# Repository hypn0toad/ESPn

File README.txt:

This project consists of a multi platform communication device that was intended to be used as a gift / could be considered an art project. 

arduino_main/    = the main arduino code for the devices
arduino_slave/   = test code to be used in a prototype system. allows a serial interface on the PC (uart) to communicate through the arduino back and forth from an imp
imp/            = the imp code, needs to be loaded in the planner to both imps
docs/           = partslist/BOM, pinout reference, issue tracking (future ideas & bugs)
docs/datasheets = random datasheets for parts used in the design
docs/schematics = schematic and PWB for main board; schematic for logic level slave board

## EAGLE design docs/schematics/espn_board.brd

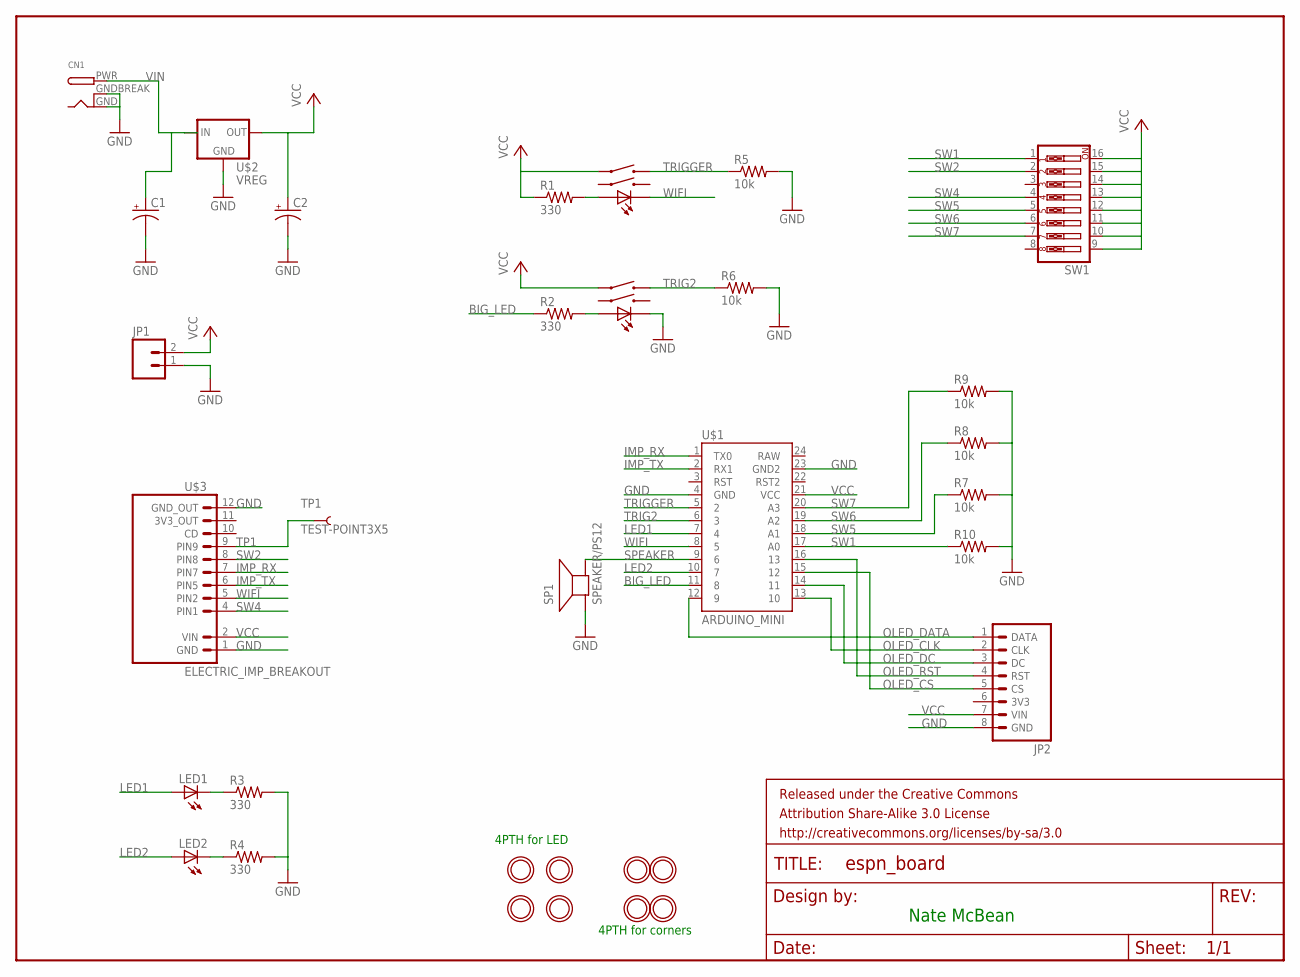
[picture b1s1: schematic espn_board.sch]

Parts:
ACK: LED_TACTILE_BUTTON
C1, C2: CAP_POLPTH2; CPOL-RADIAL-10UF-25V
CN1: DCBARRELPTH; DCJACK_2MM_PTH
FRAME1: FRAME-LETTER; CREATIVE_COMMONS
JP1: M02PTH; 1X02
JP2: OLED128X641X08; OLED_128X64
LED1, LED2: LED5MM
R1, R2, R3, R4: 330; R0805
R5, R6, R7, R8, R9, R10: 10k; R0805
SEND: LED_TACTILE_BUTTON
SP1: SPEAKER/PS12; PS12
SW1: SW_DIP-8; DIPSWITCH-08
TP1: TEST-POINT3X5; PAD.03X.05
U$1: ARDUINO_MINI
U$2: VREG; 78XXL
U$3: ELECTRIC_IMP_BREAKOUT
U$5, U$6, U$7, U$8, U$9, U$10, U$11, U$12: MOUNTINGHOLE2.5; MOUNTINGHOLE_2.5_PLATED

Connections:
BIG_LED: R2.1, U$1.11 (8)
GND: ACK.LEDC, C1.2 (-), C2.2 (-), CN1.GND, CN1.GNDBREAK, JP1.1, JP2.8 (GND), R3.2, R4.2, R5.2, R6.2, R7.2, R8.2, R9.2, R10.2, SP1.P$1 (+), U$1.4 (GND), U$1.23 (GND2), U$2.IN (GND), U$3.1 (GND), U$3.12 (GND_OUT)
IMP_RX: U$1.1 (TX0), U$3.7 (PIN7)
IMP_TX: U$1.2 (RX1), U$3.6 (PIN5)
LED1: LED1.A, U$1.7 (4)
LED2: LED2.A, U$1.10 (7)
unnamed: R1.2, SEND.LEDA
unnamed: ACK.LEDA, R2.2
unnamed: LED1.K (C), R3.1
unnamed: LED2.K (C), R4.1
OLED_CLK: JP2.2 (CLK), U$1.13 (10)
OLED_CS: JP2.5 (CS), U$1.15 (12)
OLED_DATA: JP2.1 (DATA), U$1.12 (9)
OLED_DC: JP2.3 (DC), U$1.14 (11)
OLED_RST: JP2.4 (RST), U$1.16 (13)
SPEAKER: SP1.P$2 (-), U$1.9 (6)
SW1: R10.1, SW1.1, U$1.17 (A0)
SW2: SW1.2, U$3.8 (PIN8)
SW4: SW1.4, U$3.4 (PIN1)
SW5: R7.1, SW1.5, U$1.18 (A1)
SW6: R8.1, SW1.6, U$1.19 (A2)
SW7: R9.1, SW1.7, U$1.20 (A3)
TP1: TP1.P$1, U$3.9 (PIN9)
TRIG2: ACK.SWA2, R6.1, U$1.6 (3)
TRIGGER: R5.1, SEND.SWA2, U$1.5 (2)
VCC: ACK.SWA1, C2.1 (+), JP1.2, JP2.7 (VIN), R1.1, SEND.SWA1, SW1.9, SW1.10, SW1.11, SW1.12, SW1.13, SW1.14, SW1.15, SW1.16, U$1.21 (VCC), U$2.GND (OUT), U$3.2 (VIN)
VIN: C1.1 (+), CN1.PWR, U$2.OUT (IN)
WIFI: SEND.LEDC, U$1.8 (5), U$3.5 (PIN2)

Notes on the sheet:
Nate McBean
4PTH for LED
4PTH for corners

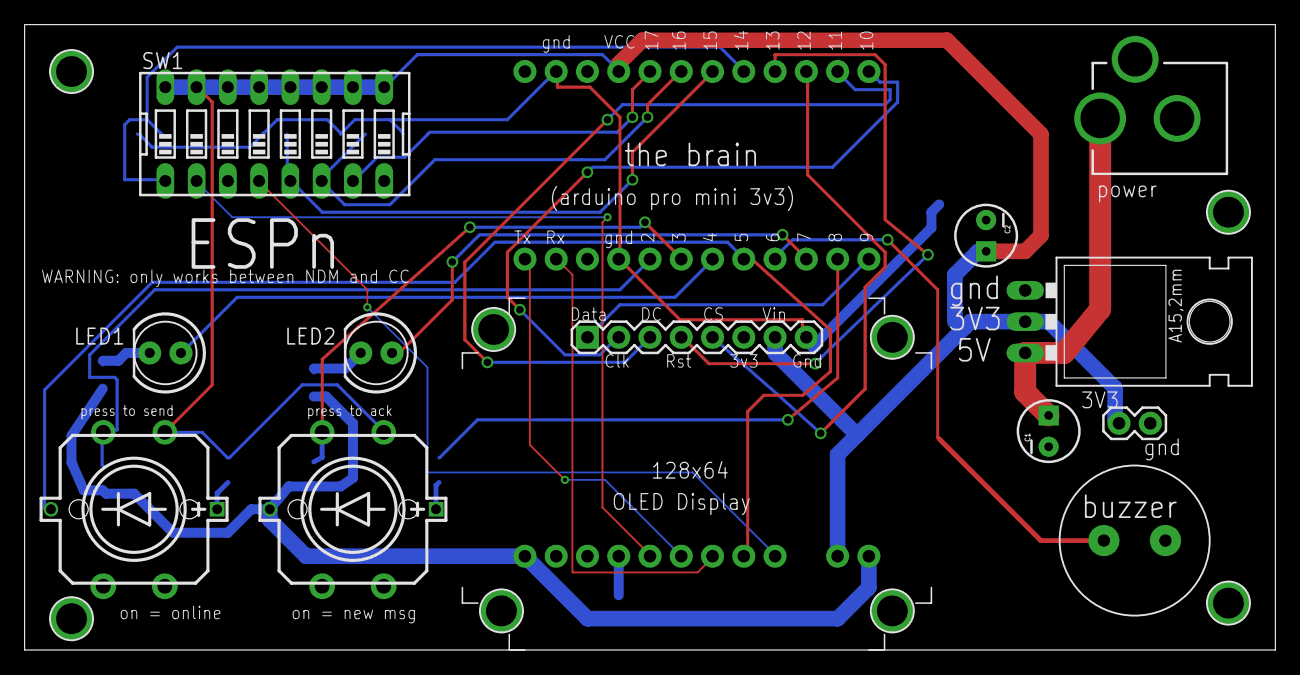
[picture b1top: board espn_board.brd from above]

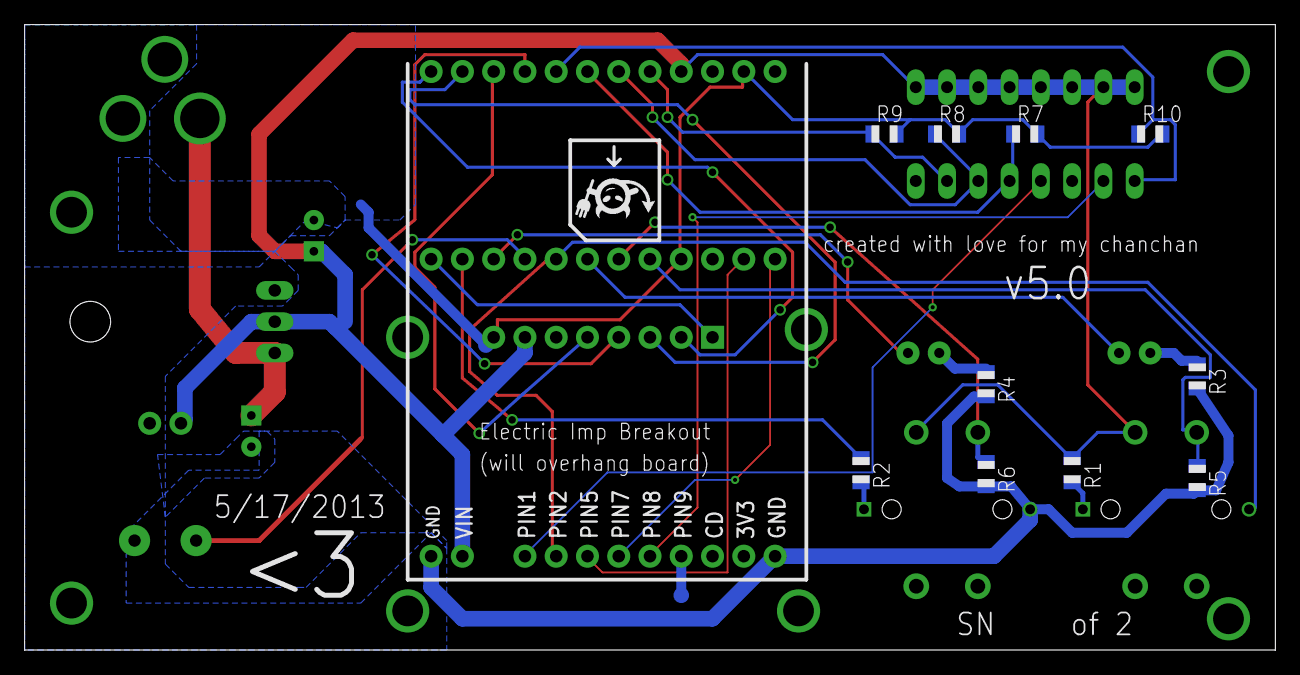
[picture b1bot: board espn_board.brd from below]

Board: 2 copper layers, 101.6 x 50.8 mm, 34 parts (12 on the bottom side), 28 nets.

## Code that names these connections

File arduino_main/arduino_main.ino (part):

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

/*** pin definitions ***/
#define OLED_DC         11
#define OLED_CS         12
#define OLED_CLK        10
#define OLED_MOSI       9
#define OLED_RESET      13
#define SPEAKER_PIN     6
#define WIFI_STATUS_PIN 5

#define LED1_PIN    4
#define LED2_PIN    7
#define ACK_LED_PIN 8
#define TX_BUT_PIN  2
#define ACK_BUT_PIN 3
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  stingy_mode = true;
  happy_mode  = false;
  
  // setup wifi status pin
  pinMode(WIFI_STATUS_PIN, INPUT);
  digitalWrite(WIFI_STATUS_PIN, 1);
  
  // setup other pins
  pinMode(LED1_PIN,    OUTPUT);
  pinMode(LED2_PIN,    OUTPUT);
  pinMode(ACK_LED_PIN, OUTPUT);
  pinMode(TX_BUT_PIN,  INPUT);
  pinMode(ACK_BUT_PIN, INPUT);
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void beep() {
  int delayms = 50;
  
  analogWrite(SPEAKER_PIN, 20);      // Almost any value can be used except 0 and 255
  delay(delayms);                    // wait for a delayms ms
  analogWrite(SPEAKER_PIN, 0);       // 0 turns it off
  delay(delayms);                    // wait for a delayms ms   
  
  analogWrite(SPEAKER_PIN, 20);      // Almost any value can be used except 0 and 255
  delay(delayms);                    // wait for a delayms ms
  analogWrite(SPEAKER_PIN, 0);       // 0 turns it off
  delay(delayms);                    // wait for a delayms ms 
  
  analogWrite(SPEAKER_PIN, 20);      // Almost any value can be used except 0 and 255
  delay(delayms);                    // wait for a delayms ms
  analogWrite(SPEAKER_PIN, 0);       // 0 turns it off
  delay(delayms);                    // wait for a delayms ms   
}

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  // temporarily comment out this code to save some valuable SRAM
  if( debugio ) {
    // // Blink some LEDs
    // digitalWrite(LED1_PIN, flash_led_status);
    // digitalWrite(LED2_PIN, flash_led_status);
    // digitalWrite(ACK_LED_PIN, flash_led_status);
    // flash_led_status = !flash_led_status;
    
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  // initiate SHAME_LED when haven't txed in TX_AGE
  if( (last_tx_timestamp == 0) || this_second > (last_tx_timestamp + age_for_low_tx)) {
    stingy_mode = true;  
    digitalWrite(LED2_PIN,1);
  } else {
    stingy_mode = false;
    digitalWrite(LED2_PIN,0);
  }

  
  // initiate HAPPY_LED when have rx'ed in RX_AGE
  if ((last_rx_timestamp == 0) || this_second > (last_rx_timestamp + age_for_low_rx)) {
    happy_mode = false;
    digitalWrite(LED1_PIN,0);
  } else {
    happy_mode = true;
    digitalWrite(LED1_PIN,1);
  }  
}

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
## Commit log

2013-04-01 Initial Release
    This just has a OLED display and a piezo buzzer connected to an arduino.
    Think of it as a "first step" program. It doesn't do anything snazzy,
    but it works!
2013-04-02 PC UART to OLED
    Added PC UART to OLED display. Note will display when you end with the |
    character (not a newline). Also, note that the next step is to respond
    to Serial1 (on the leonardo.. on pro mini will probably be Serial) which
    should have comm from the Electric Imp.
2013-04-02 Welcome to the cloud
    Now the UART is received from the cloud (from the imp.php website form
    POST) and then is transmitted from the imp over UART to the arduino. The
    arduino then displays it just the same as if it received it from a local
    PC. Baud rate of 9600 didn't seem to work but 19200 seems fine (odd..)
2013-04-03 OLED Health Bar + Piezo
    Added piezo beeping. Added health bar display and timeout.
2013-04-05 Update for Arduino Pro Mini
    Received and switched code to work for an Arduino Pro Mini (Running at
    3V3). Works great! (only had to switch away from the dual serials
    available on the Leonardo)
2013-04-07 Added slave leonardo for testing purposes
    This release allows two imps to talk to each other. The sparkfun UART
    code has been upgraded to use a callback function. The slave setup will
    receive from the imp and display in a serial console. It will also
    transmit serial commands from the console out over the imp. Fully
    working checkin. Also added some datasheets and a schematic for the
    slave setup.
2013-04-07 Addition of online status
    Will now light up an LED from the IMP when connected to wifi. Arduino
    connects to this indicator to also know when online.
2013-04-08 Added Trigger Button
    New! Trigger button on slave arduino (well will be on master as well
    eventually). Sends an automatic serial message. "Debounced" to trigger a
    max of once a second.
2013-04-10 Initial Schematic
    All components placed. Not fully connected / board unrouted.
2013-04-10 Initial Layout
    Schematic completely wired. Have initial placement (no routing)
2013-04-10 Fixed pinout on OLED
    Oops! That would have been a horrible mistake. I also messed around with
    routing some.
2013-04-10 Layout Work
    More work on the layout. I pretty carefully managed power to from the DC
    header to the VREG to the Imp (by FAR the biggest power consumer on the
    board). I also rearranged some parts to try to optimize placement. Next
    up- auto route.
2013-04-29 Final Built Board
    Final built board schematic + layout (received board already, tested,
    works). Added IO pins to the arduino code, works.
2013-05-05 Button Comms Working
    Successfully sends a message to the other device when press a button
    (switched communication protocol). Woot woot
2013-05-06 Companion Detection
    Modified timestamps to now record time in seconds (try to prevent
    overflow with the poor arduino's integers). Now the devices ping each
    other, and have a display based on system status. icon in corner
    indicates system health.
2013-05-07 Age Tracking
    Switched to use char arrays instead of strings (strings got corrupted).
    This is more efficient anyways. Added OLED display of ages. Track ping
    (tx/rx) and regular tx/rx. Light LED when haven't txed in a while (12h).
2013-05-07 Health Bar Update
    Now health bar displays time since last status update from other device.
2013-05-09 Failure Text
    Stupid arduino having limited memory. This (when uncommented) glitched
    the poor thing like crazy. I'm committing it just so i have it in
    revision history.
2013-05-09 Code Cleanup and Nicer Rx Age
    Rearranged some code and cleaned some stuff up. This is rev 1.0 on the
    device. Have a list of stuff to do still (oh well) but this will be
    final unless something comes up. Added more human readable RX age (h m s
    instead of just s). Looks good!
2013-05-23 Cleanup
    Renamed files (sorry git), cleaned up comments.
2013-06-09 Doc Additions
    Added BOM, added Pinout Reference, added issue tracking text file
2013-06-10 Imp Planner Graphic
    Added a graphic to display Imp planner connections.

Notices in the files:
parts and their libraries:
SparkFun-Boards: Licensing: CC v3.0 Share-Alike You are welcome to use this library for commercial purposes.
SparkFun-Aesthetics: Released under the Creative Commons Attribution Share-Alike 3.0 License
SparkFun-Aesthetics: http://creativecommons.org/licenses/by-sa/3.0
